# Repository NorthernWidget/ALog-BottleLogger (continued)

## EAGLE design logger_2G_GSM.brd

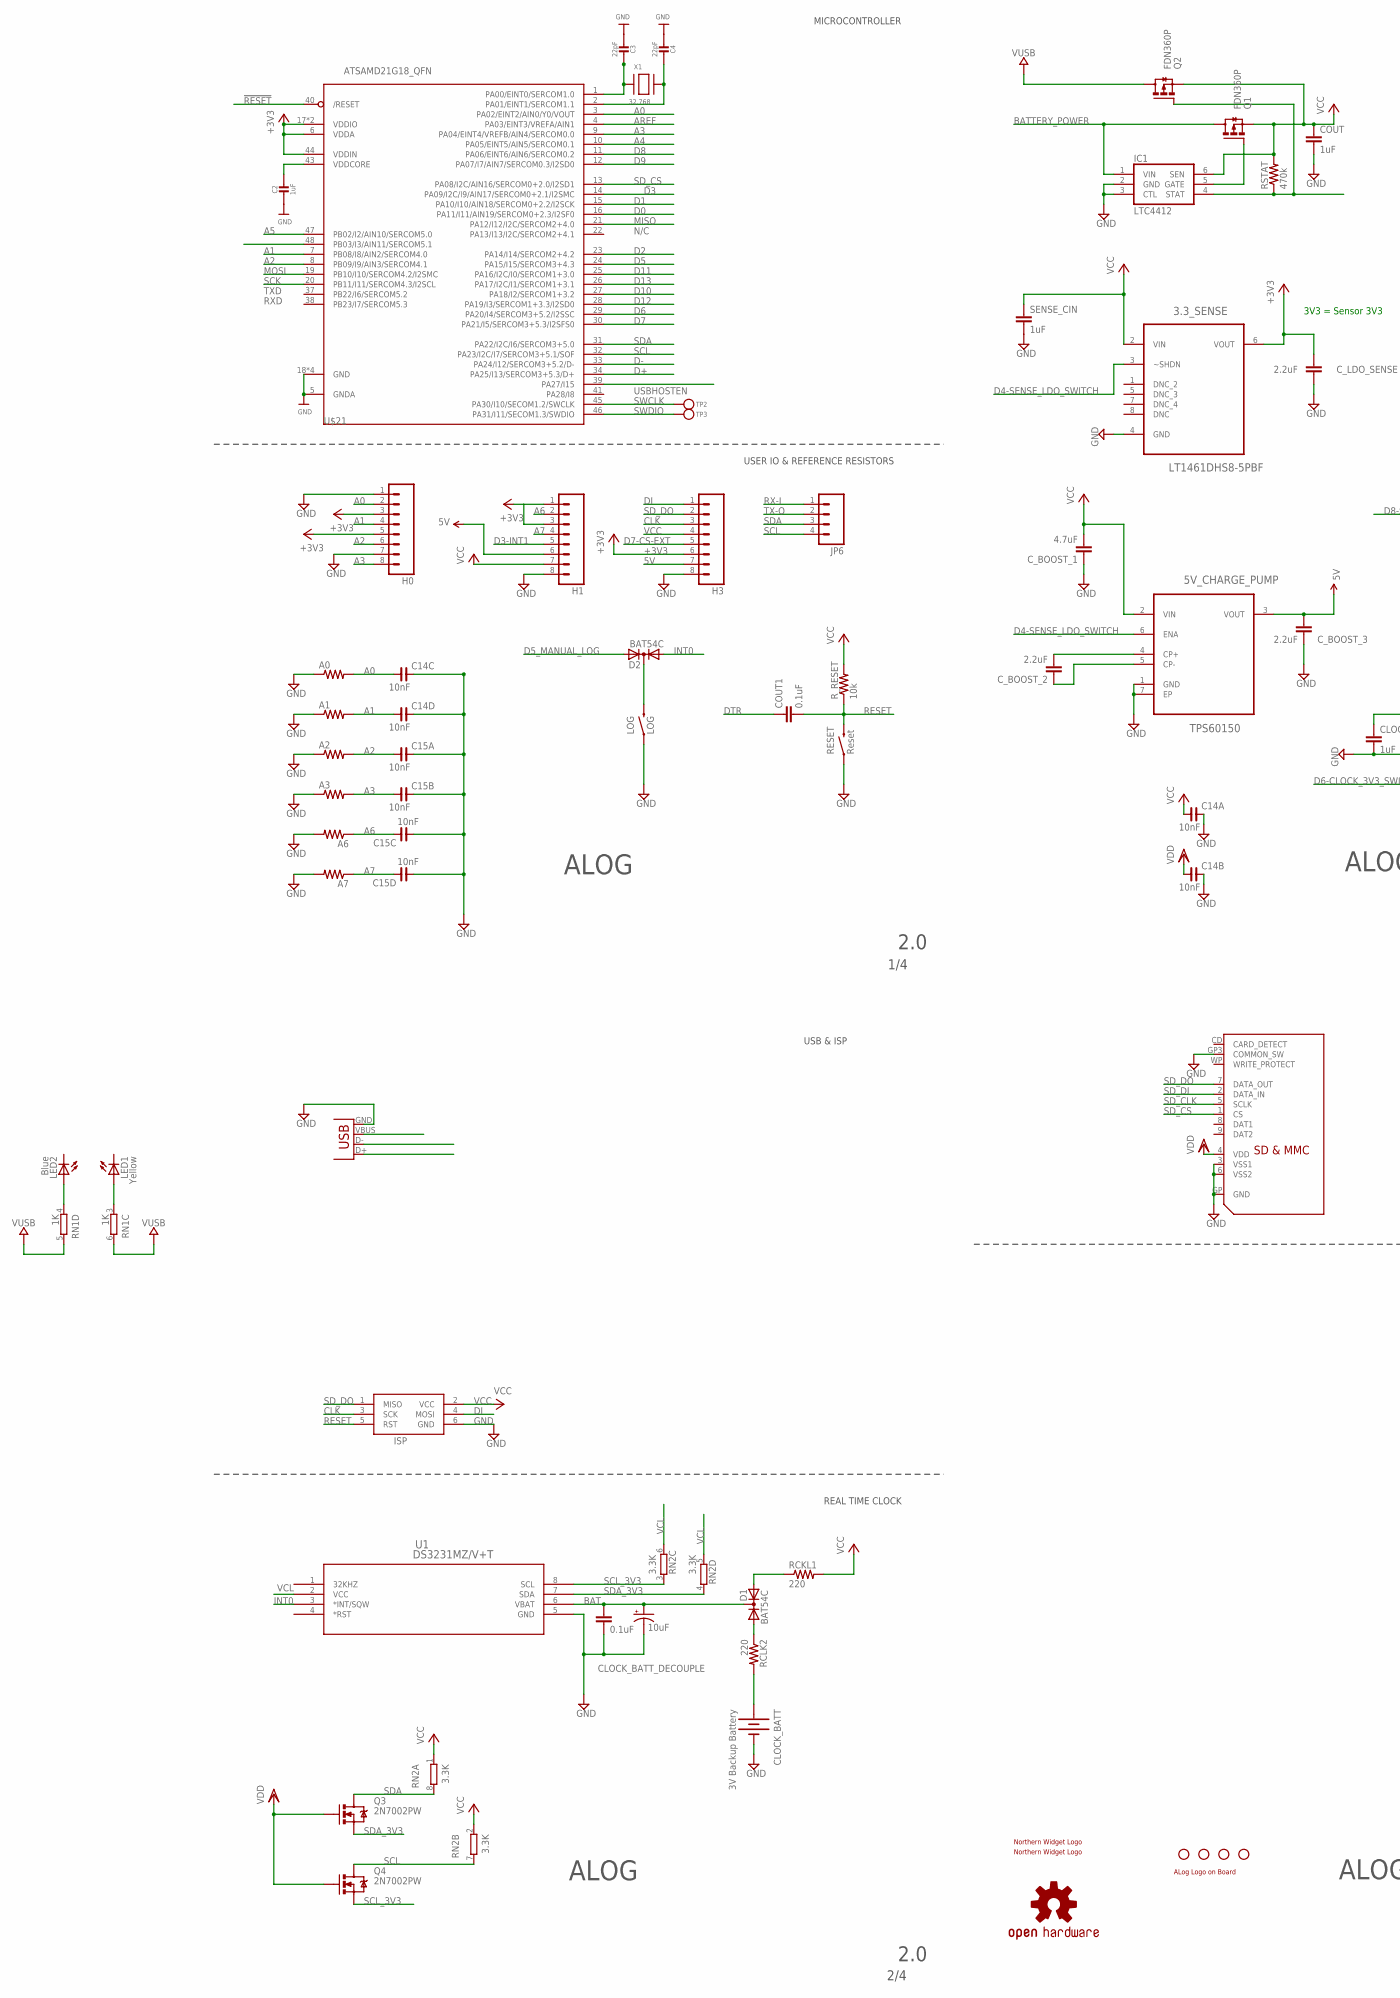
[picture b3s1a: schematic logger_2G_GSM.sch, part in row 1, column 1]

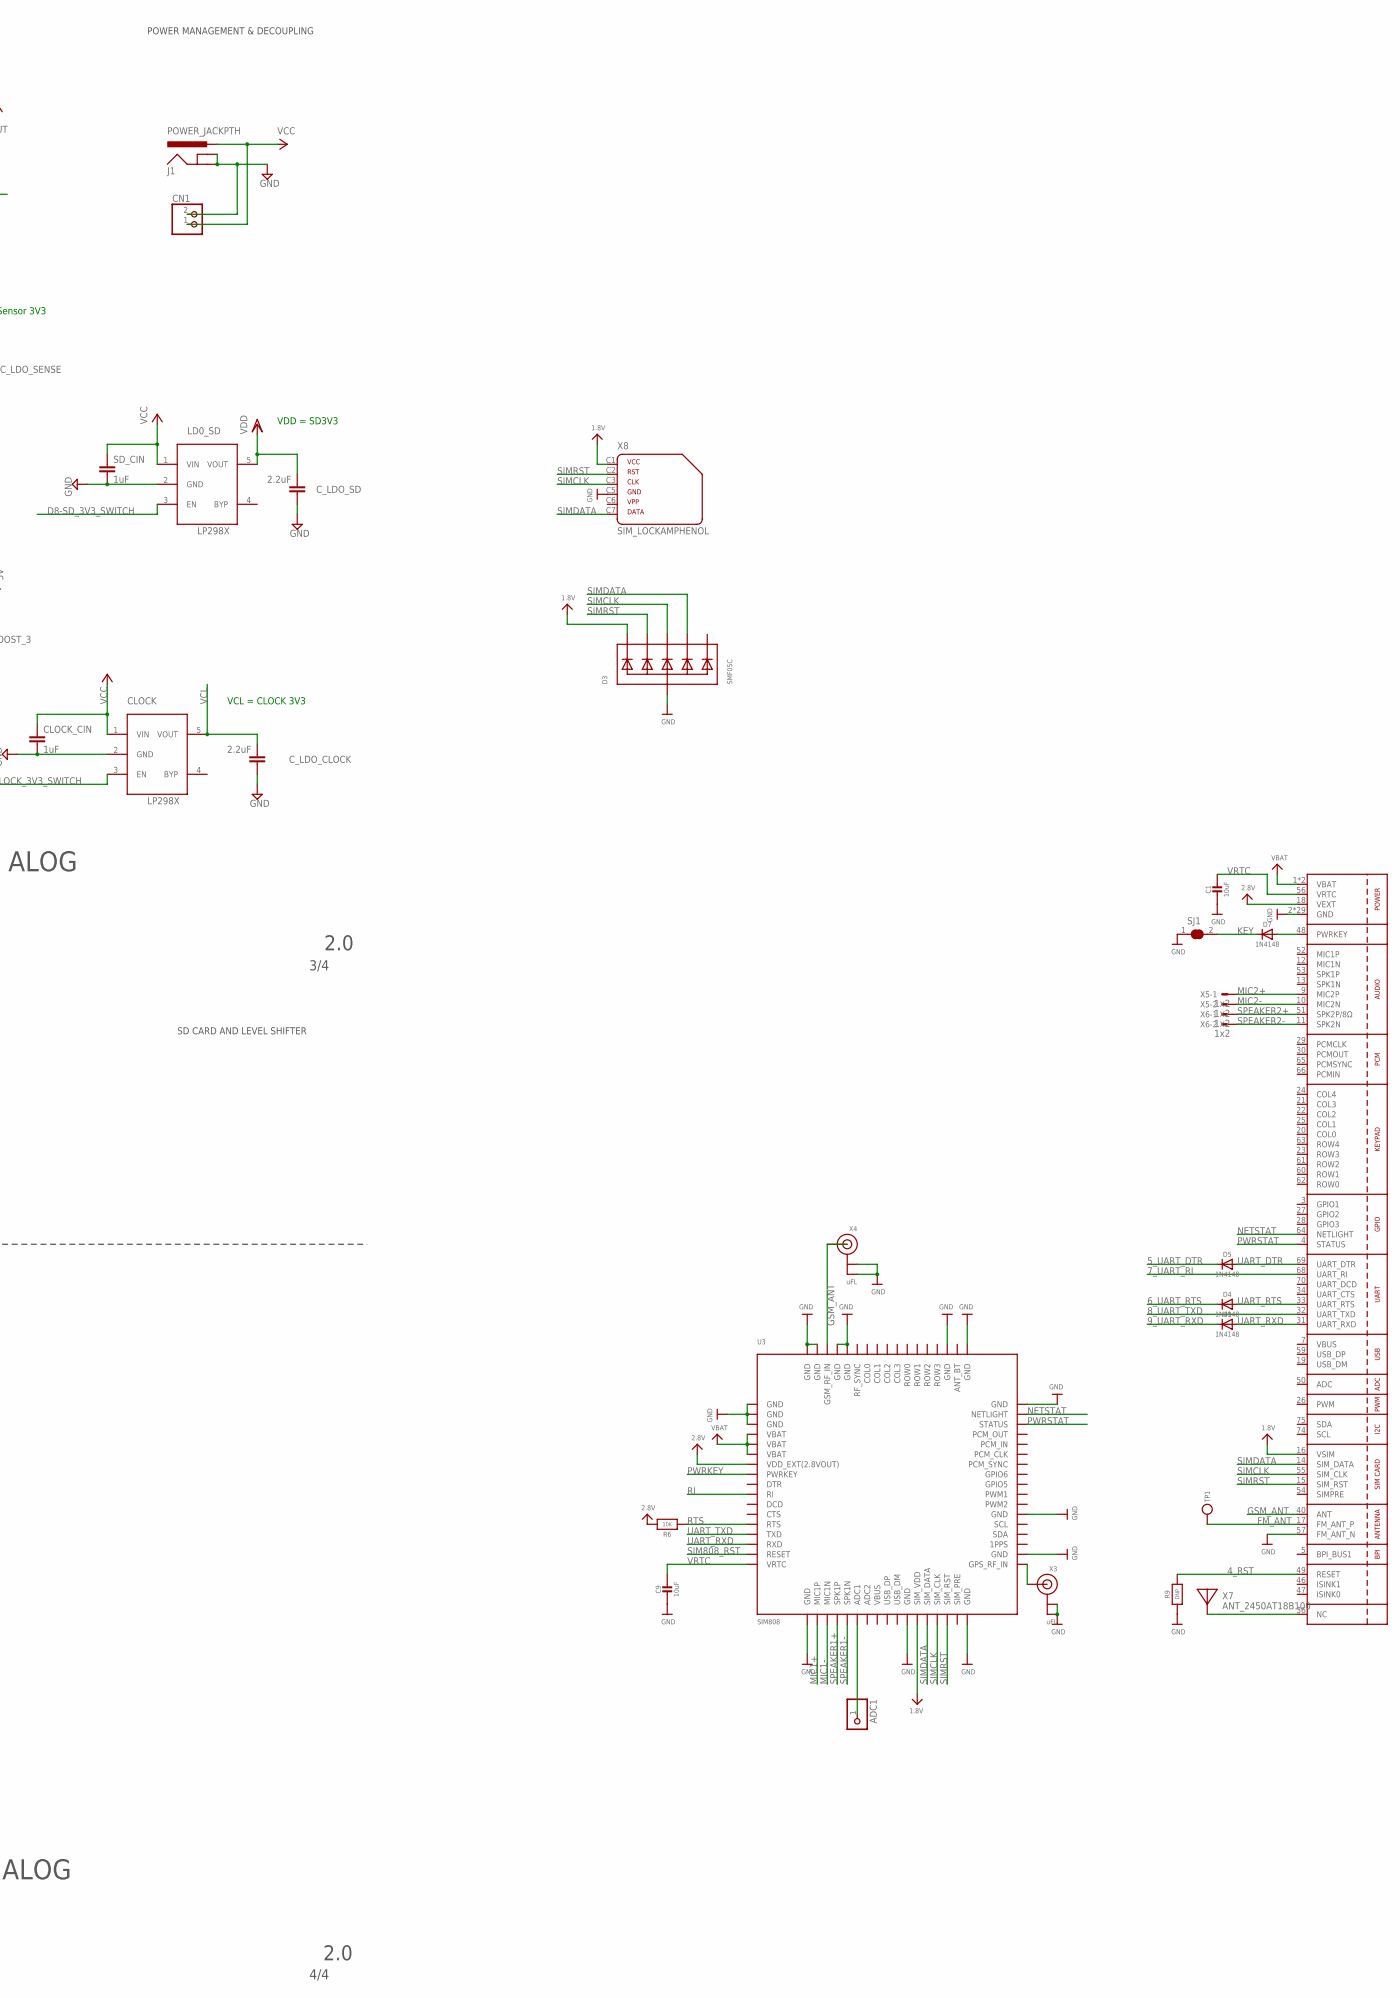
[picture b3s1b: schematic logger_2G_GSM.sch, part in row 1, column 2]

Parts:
3.3_SENSE: LT1461DHS8-5PBF; SOIC127P600X175-8N
5V_CHARGE_PUMP: TPS60150; SON65P200X200X80-7N
A0, A1, A2, A3, A6, A7: R-US_0207/10; 0207/10
ADC1: PINHD-1X1CB; 1X01-CLEANBIG
C1: 10uF; _0805MP
C2: 1uF; 0603-NO
C3, C4: 22pF; 0603-NO
C9: 10uF; 0805-NO
C14, C15: 10nF; CECJ-1206
CLOCK: LP2985; SOT23-5L
CLOCK_BATT: 3V Backup Battery; BATTCON_12MM_PTH
CLOCK_BATT_DECOUP: 0.1uF; C0603
CLOCK_BATT_DECOUPLE: 10uF; EIA3216
CLOCK_CIN: 1uF; C0603
CN1: JST_2PIN-THM; JST-PH-2-THM
COUT: 1uF; C0603
COUT1: 0.1uF; C0603
C_BOOST_1: 4.7uF; C0603
C_BOOST_2, C_BOOST_3: 2.2uF; C0603
C_LDO_CLOCK: 2.2uF; C0603
C_LDO_SD: 2.2uF; C0603
C_LDO_SENSE: 2.2uF; C0603
D1, D2: BAT54C; SOT23C
D3: SMF05C; SOT363
D4, D5, D7, D9: 1N4148; SOD-323
H0, H1, H3: M083.5MM-8; SCREWTERMINAL-3.5MM-8
IC1: LTC4412; TSOT23-6
ISP: AVRISP-6; AVRISP
J1: POWER_JACKPTH; POWER_JACK_PTH
JP1, JP2, JP3, JP4: STAND-OFF
JP5: USB-B; USB-B-PTH
JP6: M04SCREW; SCREWTERMINAL-3.5MM-4
LD0_SD: LP2985; SOT23-5L
LED1: Yellow; LED-0603
LED2: Blue; LED-0603
LOG: LOG; TACTILE-PTH
LOGO1: OSHW-LOGOM; OSHW-LOGO-M
Q1, Q2: FDN360P; SUPER-SOT3
Q3, Q4: 2N7002PW; SOT323
R6: 10K; 0805-NO
R9: DNP; 0603-NO
RCKL1: 220; R0603
RCLK2: 220; R0603
RESET: Reset; TACTILE-PTH
RN1: 1K; 0603-ARC
RN2: 3.3K; 0603-ARC
RSTAT: 470k; R0603
R_RESET: 10k; R0603
SD: SDMMC06132; 06132
SD_CIN: 1uF; C0603
SENSE_CIN: 1uF; C0603
SJ1: SOLDERJUMPER_CLOSED; SOLDERJUMPER_CLOSEDWIRE
TP1, TP2, TP3: TESTPOINTROUND1.5MM; TESTPOINT_ROUND_1.5MM
U1: DS3231MZ/V+T; 21-0041B_8
U2: SIM800H/L; SIM800L
U3: SIM808; SIM900_SMT
U$1: NWLOGO
U$2: ALOG_LOGO_V1_5.5MM; ALOG_LOGO_V1_SMALL
U$3: NWLOGO_MED
U$21: ATSAMD21G18_QFN; TQFN48_7MM
X1: 32.768; XTAL3215
X3, X4: uFL; U.FL
X5, X6: 1x2; 87758-0216
X7: ANT_2450AT18B100
X8: SIM_LOCKAMPHENOL; C707_10M006_512_2

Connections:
1.8V: D3.1 (C1), U2.16 (VSIM), U3.P$29 (SIM_VDD), X8.C1 (1)
2.8V: R6.2, U2.18 (VEXT), U3.P$7 (VDD_EXT(2.8VOUT))
4_RST: R9.2, U2.49 (RESET)
5V: 5V_CHARGE_PUMP.3 (VOUT), C_BOOST_3.2, H1.6, H3.7
5_UART_DTR: D5.C
6_UART_RTS: D4.C
7_UART_RI: U2.68 (UART_RI)
8_UART_TXD: U2.32 (UART_TXD)
9_UART_RXD: D9.C
!RESET: U$21.40 (/RESET)
+3V3: 3.3_SENSE.6 (VOUT), C_LDO_SENSE.2, H0.3, H0.5, H1.1, H1.3, H3.6, U$21.6 (VDDA), U$21.17 (VDDIO), U$21.36 (VDDIO), U$21.44 (VDDIN)
A0: A0.2, C14.C1 (1), H0.2, U$21.3 (PA02/EINT2/AIN0/Y0/VOUT)
A1: A1.2, C14.D1 (1), H0.4, U$21.7 (PB08/I8/AIN2/SERCOM4.0)
A2: A2.2, C15.A1 (1), H0.6, U$21.8 (PB09/I9/AIN3/SERCOM4.1)
A3: A3.2, C15.B1 (1), H0.8, U$21.9 (PA04/EINT4/VREFB/AIN4/SERCOM0.0)
A4: U$21.10 (PA05/EINT5/AIN5/SERCOM0.1)
A5: U$21.47 (PB02/I2/AIN10/SERCOM5.0)
A6: A6.1, C15.C2 (2), H1.2
A7: A7.1, C15.D2 (2), H1.4
AREF: U$21.4 (PA03/EINT3/VREFA/AIN1)
BAT: CLOCK_BATT_DECOUP.1, CLOCK_BATT_DECOUPLE.A (+), D1.3 (K), U1.6 (VBAT)
BATTERY_POWER: IC1.1 (VIN), Q1.3 (D)
CLK: H3.3, ISP.3 (SCK)
D0: U$21.16 (PA11/I11/AIN19/SERCOM0+2.3/I2SF0)
D1: U$21.15 (PA10/I10/AIN18/SERCOM0+2.2/I2SCK)
D2: U$21.23 (PA14/I14/SERCOM2+4.2)
D3: U$21.14 (PA09/I2C/I9/AIN17/SERCOM0+2.1/I2SMC)
D3-INT1: H1.5
D4-SENSE_LDO_SWITCH: 3.3_SENSE.3 (~SHDN), 5V_CHARGE_PUMP.6 (ENA)
D5: U$21.24 (PA15/I15/SERCOM3+4.3)
D5_MANUAL_LOG: D2.2 (A2)
D6: U$21.29 (PA20/I4/SERCOM3+5.2/I2SSC)
D6-CLOCK_3V3_SWITCH: CLOCK.3 (EN)
D7: U$21.30 (PA21/I5/SERCOM3+5.3/I2SFS0)
D7-CS-EXT: H3.5
D8: U$21.11 (PA06/EINT6/AIN6/SERCOM0.2)
D8-SD_3V3_SWITCH: LD0_SD.3 (EN)
D9: U$21.12 (PA07/I7/AIN7/SERCOM0.3/I2SD0)
D10: U$21.27 (PA18/I2/SERCOM1+3.2)
D11: U$21.25 (PA16/I2C/I0/SERCOM1+3.0)
D12: U$21.28 (PA19/I3/SERCOM1+3.3/I2SD0)
D13: U$21.26 (PA17/I2C/I1/SERCOM1+3.1)
D+: U$21.34 (PA25/I13/SERCOM3+5.3/D+)
D-: U$21.33 (PA24/I12/SERCOM3+5.2/D-)
DI: H3.1, ISP.4 (MOSI)
DTR: COUT1.1
FM_ANT: TP1.P$1, U2.17 (FM_ANT_P)
GND: 3.3_SENSE.4 (GND), 5V_CHARGE_PUMP.1 (GND), 5V_CHARGE_PUMP.7 (EP), A0.1, A1.1, A2.1, A3.1, A6.2, A7.2, C1.2, C2.2, C3.2, C4.2, C9.2, C14.A2 (2), C14.B2 (2), C14.C2 (2), C14.D2 (2), C15.A2 (2), C15.B2 (2), C15.C1 (1), C15.D1 (1), CLOCK.2 (GND), CLOCK_BATT.GND (-), CLOCK_BATT_DECOUP.2, CLOCK_BATT_DECOUPLE.C (-), CLOCK_CIN.2, CN1.2 (1), COUT.2, C_BOOST_1.1, C_BOOST_3.1, C_LDO_CLOCK.1, C_LDO_SD.1, C_LDO_SENSE.1, D3.2 (A), H0.1, H0.7, H1.8, H3.8, IC1.2 (GND), IC1.3 (CTL), ISP.6 (GND), J1.GND, J1.GNDBREAK, JP5.GND, LD0_SD.2 (GND), LOG.1, R9.1, RESET.1, SD.3 (VSS1), SD.6 (VSS2), SD.GP (GND), SD.GP3 (COMMON_SW), SD_CIN.2, SENSE_CIN.2, SJ1.1, U1.5 (GND), U2.2 (GND), U2.6 (GND), U2.8 (GND), U2.35 (GND), U2.37 (GND), U2.38 (GND), U2.39 (GND), U2.41 (GND), U2.43 (GND), U2.44 (GND), U2.45 (GND), U2.57 (FM_ANT_N), U2.58 (GND), U2.67 (GND), U2.71 (GND), U2.72 (GND), U2.73 (GND), U2.76 (GND), U2.77 (GND), U2.78 (GND), U2.79 (GND), U2.80 (GND), U2.81 (GND), U2.82 (GND), U2.83 (GND), U2.84 (GND), U2.85 (GND), U2.86 (GND), U2.87 (GND), U2.88 (GND), U3.P$1 (GND), U3.P$2 (GND), U3.P$3 (GND), U3.P$18 (GND), U3.P$28 (GND), U3.P$34 (GND), U3.P$36 (GND), U3.P$40 (GND), U3.P$51 (GND), U3.P$52 (GND), U3.P$54 (GND), U3.P$64 (GND), U3.P$65 (GND), U3.P$67 (GND), U3.P$68 (GND), U$21.5 (GNDA), U$21.18 (GND), U$21.35 (GND), U$21.42 (GND), U$21.THERMAL (GND), X3.1 (GND), X3.2 (GND), X4.1 (GND), X4.2 (GND), X8.C5 (4)
GSM_ANT: U2.40 (ANT), U3.P$66 (GSM_RF_IN), X4.3 (SIGNAL)
INT0: D2.1 (A1), U1.3 (*INT/SQW)
KEY: D7.C, SJ1.2
MIC1+: U3.P$19 (MIC1P)
MIC1-: U3.P$20 (MIC1N)
MIC2+: U2.9 (MIC2P), X5.1
MIC2-: U2.10 (MIC2N), X5.2
MISO: U$21.21 (PA12/I12/I2C/SERCOM2+4.0)
MOSI: U$21.19 (PB10/I10/SERCOM4.2/I2SMC)
unnamed: D1.1 (A1), RCLK2.1
unnamed: CLOCK_BATT.VCC@1 (+), RCLK2.2
unnamed: LED2.A, RN1.4 (1)
unnamed: U3.P$35 (GPS_RF_IN), X3.3 (SIGNAL)
unnamed: IC1.4 (STAT), Q2.1 (G), RSTAT.1
unnamed: IC1.5 (GATE), Q1.1 (G)
unnamed: LED1.A, RN1.3 (1)
unnamed: ADC1.1, U3.P$23 (ADC1)
unnamed: D2.3 (K), LOG.3 (2)
unnamed: U2.36 (NC), X7.FP
unnamed: 5V_CHARGE_PUMP.4 (CP+), C_BOOST_2.2
unnamed: 5V_CHARGE_PUMP.5 (CP-), C_BOOST_2.1
unnamed: D7.A, U2.48 (PWRKEY)
unnamed: C3.1, U$21.1 (PA00/EINT0/SERCOM1.0), X1.P$1
unnamed: C4.1, U$21.2 (PA01/EINT1/SERCOM1.1), X1.P$2
unnamed: D1.2 (A2), RCKL1.1
NETSTAT: U2.64 (NETLIGHT), U3.P$50 (NETLIGHT)
PWRKEY: U3.P$8 (PWRKEY)
PWRSTAT: U2.4 (STATUS), U3.P$49 (STATUS)
RESET: COUT1.2, ISP.5 (RST), RESET.3 (2), R_RESET.1
RI: U3.P$10 (RI)
RTS: R6.1, U3.P$13 (RTS)
RX-I: JP6.1
SCK: U$21.20 (PB11/I11/SERCOM4.3/I2SCL)
SCL: JP6.4, Q4.3 (D), RN2.7 (2), U$21.32 (PA23/I2C/I7/SERCOM3+5.1/SOF)
SCL_3V3: Q4.2 (S), RN2.3 (1), U1.8 (SCL)
SDA: JP6.3, Q3.3 (D), RN2.8 (2), U$21.31 (PA22/I2C/I6/SERCOM3+5.0)
SDA_3V3: Q3.2 (S), RN2.4 (1), U1.7 (SDA)
SD_CLK: SD.5 (SCLK)
SD_CS: SD.1 (CS), U$21.13 (PA08/I2C/AIN16/SERCOM0+2.0/I2SD1)
SD_DI: SD.2 (DATA_IN)
SD_DO: H3.2, ISP.1 (MISO), SD.7 (DATA_OUT)
SIM808_RST: U3.P$16 (RESET)
SIMCLK: D3.4 (C3), U2.55 (SIM_CLK), U3.P$31 (SIM_CLK), X8.C3 (3)
SIMDATA: D3.5 (C4), U2.14 (SIM_DATA), U3.P$30 (SIM_DATA), X8.C7 (6)
SIMRST: D3.3 (C2), U2.15 (SIM_RST), U3.P$32 (SIM_RST), X8.C2 (2)
SPEAKER1+: U3.P$21 (SPK1P)
SPEAKER1-: U3.P$22 (SPK1N)
SPEAKER2+: U2.51 (SPK2P/8Ω), X6.1
SPEAKER2-: U2.11 (SPK2N), X6.2
SWCLK: TP2.P$1, U$21.45 (PA30/I10/SECOM1.2/SWCLK)
SWDIO: TP3.P$1, U$21.46 (PA31/I11/SECOM1.3/SWDIO)
TX-O: JP6.2
UART_DTR: D5.A, U2.69 (UART_DTR)
UART_RTS: D4.A, U2.33 (UART_RTS)
UART_RXD: D9.A, U2.31 (UART_RXD), U3.P$15 (RXD)
UART_TXD: U3.P$14 (TXD)
VBAT: U2.1 (VBAT), U2.42 (VBAT), U3.P$4 (VBAT), U3.P$5 (VBAT), U3.P$6 (VBAT)
VBUS: U2.7 (VBUS), U3.P$25 (VBUS)
VCC: 3.3_SENSE.2 (VIN), 5V_CHARGE_PUMP.2 (VIN), C14.A1 (1), CLOCK.1 (VIN), CLOCK_CIN.1, CN1.1 (2), COUT.1, C_BOOST_1.2, H1.7, H3.4, IC1.6 (SEN), ISP.2 (VCC), J1.PWR, LD0_SD.1 (VIN), Q1.2 (S), Q2.2 (S), RCKL1.2, RN2.1, RN2.2 (1), RSTAT.2, R_RESET.2, SD_CIN.1, SENSE_CIN.1
VCL: CLOCK.5 (VOUT), C_LDO_CLOCK.2, RN2.5 (2), RN2.6 (2), U1.2 (VCC)
VDD: C14.B1 (1), C_LDO_SD.2, LD0_SD.5 (VOUT), Q3.1 (G), Q4.1 (G), SD.4 (VDD)
VDDCORE: C2.1, U$21.43 (VDDCORE)
VRTC: C1.1, C9.1, U2.56 (VRTC), U3.P$17 (VRTC)
VUSB: Q2.3 (D), RN1.5 (2), RN1.6 (2)

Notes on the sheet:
VDD = SD3V3
3V3 = Sensor 3V3
VCL = CLOCK 3V3
MICROCONTROLLER
USER IO & REFERENCE RESISTORS
ALOG
USB & ISP
REAL TIME CLOCK
SD CARD AND LEVEL SHIFTER
POWER MANAGEMENT & DECOUPLING
2.0
1/4
2/4
3/4
4/4
N/C
USBHOSTEN
TXD
RXD

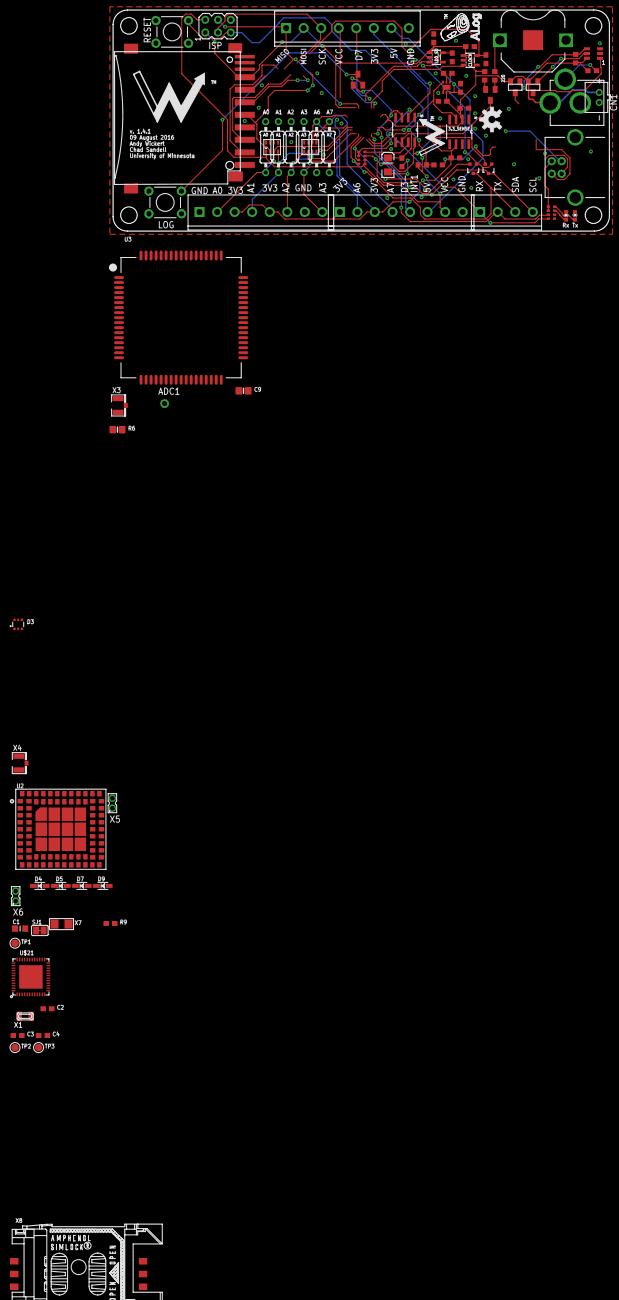
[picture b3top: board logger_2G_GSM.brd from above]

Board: 2 copper layers, 99.0 x 44.1 mm, 88 parts (0 on the bottom side), 67 nets.

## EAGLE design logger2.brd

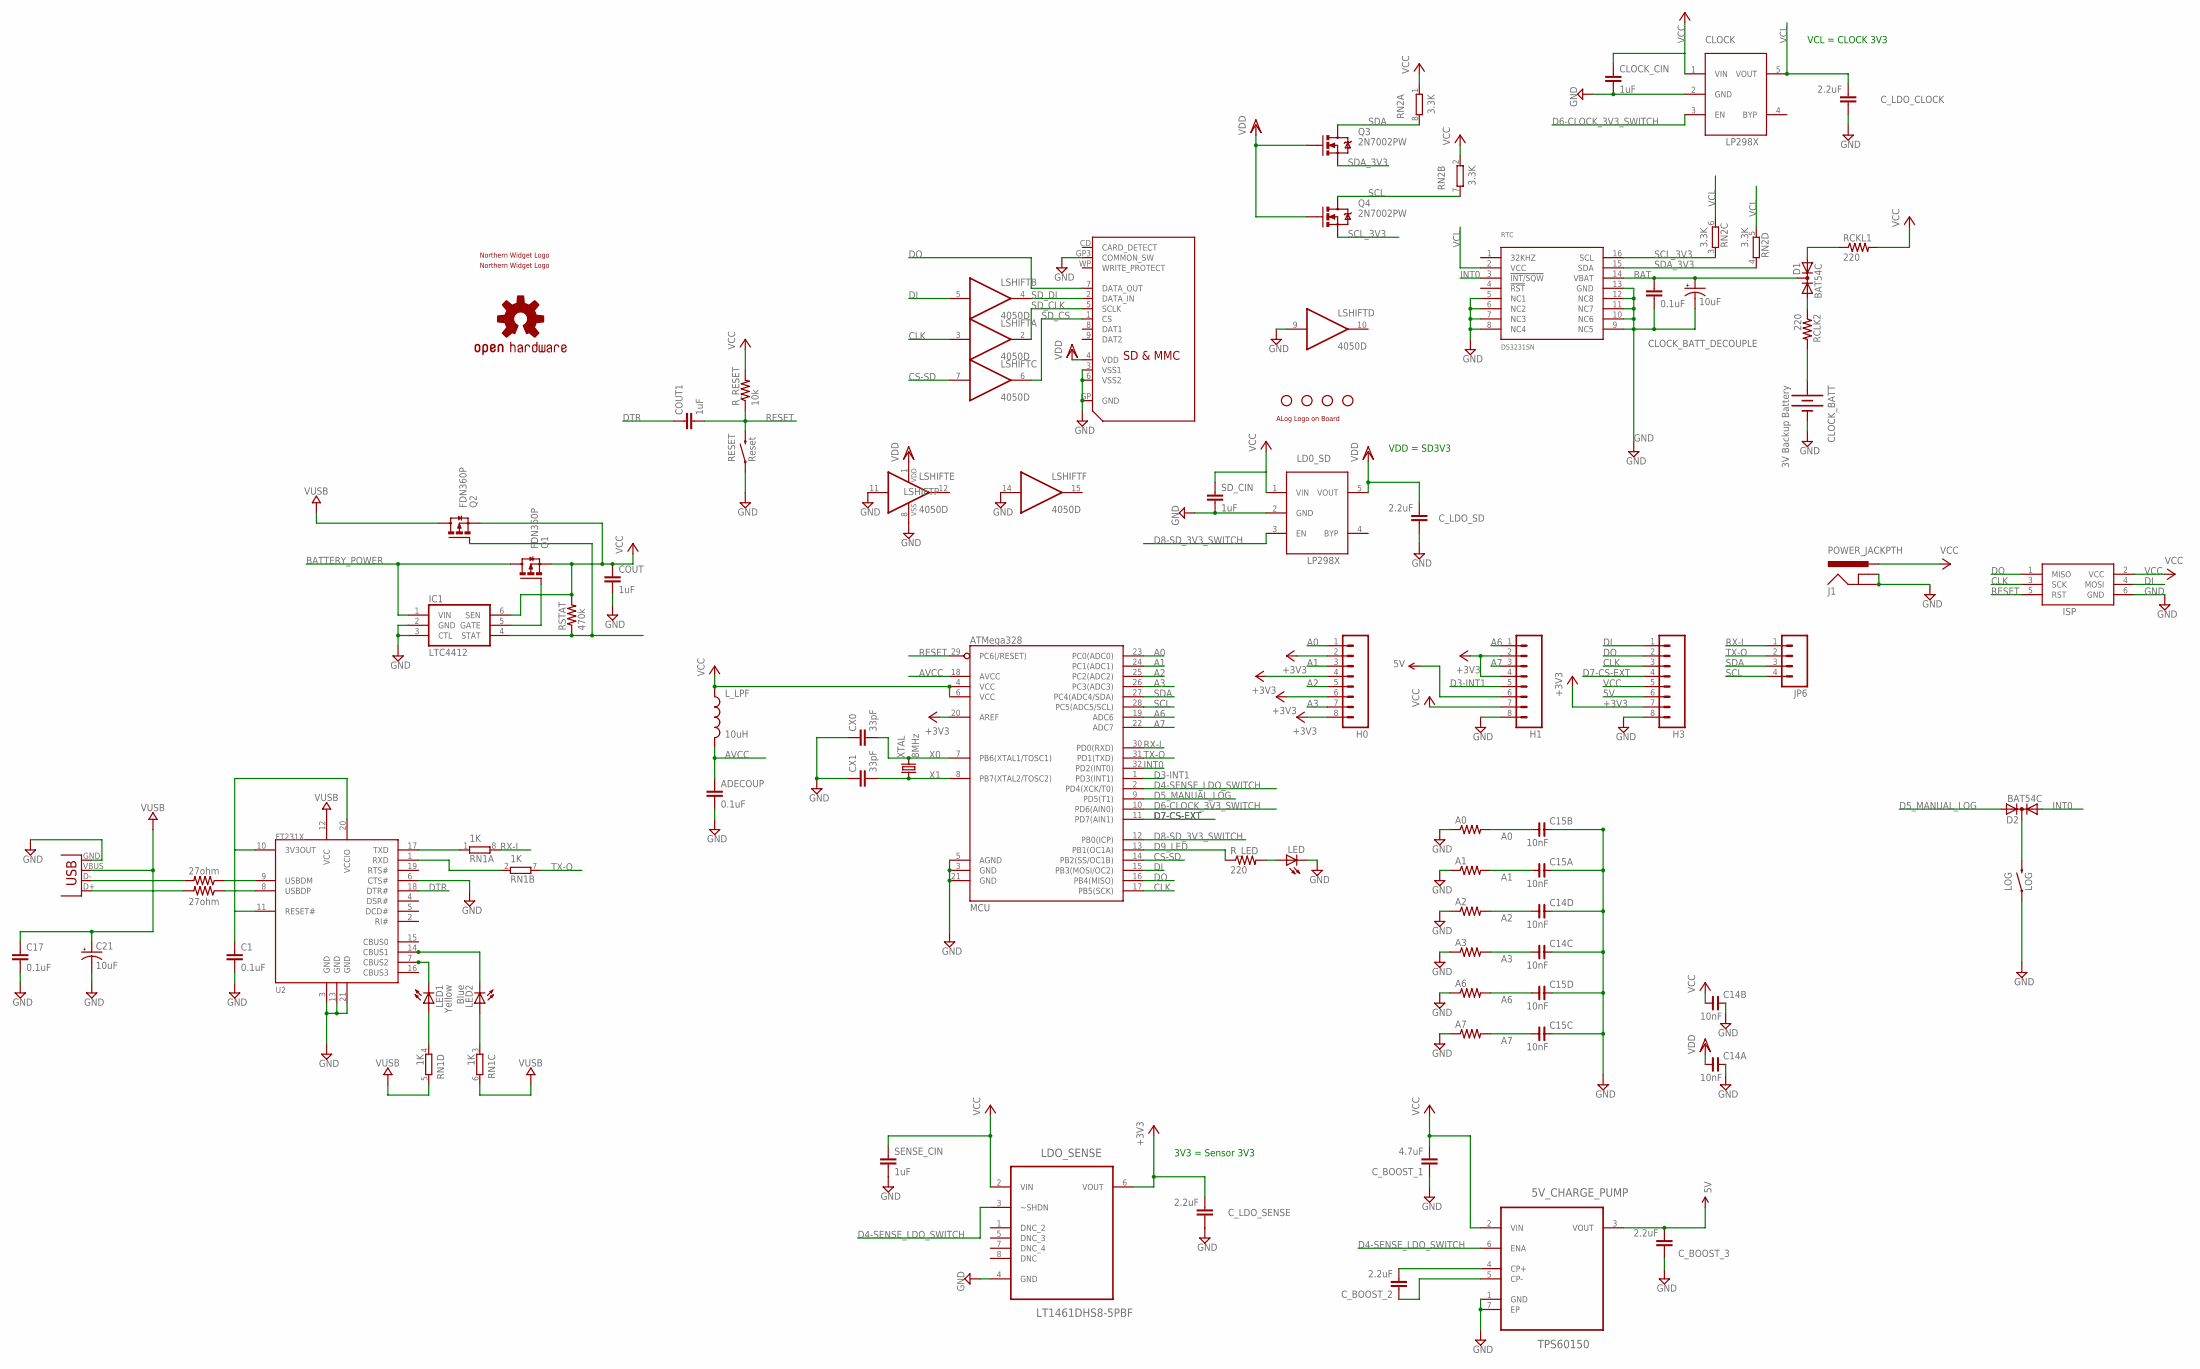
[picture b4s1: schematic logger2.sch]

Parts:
5V_CHARGE_PUMP: TPS60150; SON65P200X200X80-7N
A0, A1, A2, A3, A6, A7: R-US_0207/10; 0207/10
ADECOUP: 0.1uF; C0603
C1, C17: 0.1uF; C0603
C14, C15: 10nF; CECJ-1206
C21: 10uF; EIA3216
CLOCK: LP2985; SOT23-5L
CLOCK_BATT: 3V Backup Battery; BATTCON_12MM_PTH
CLOCK_BATT_DECOUP: 0.1uF; C0603
CLOCK_BATT_DECOUPLE: 10uF; EIA3216
CLOCK_CIN: 1uF; C0603
COUT, COUT1: 1uF; C0603
CX0, CX1: 33pF; C0603
C_BOOST_1: 4.7uF; C0603
C_BOOST_2, C_BOOST_3: 2.2uF; C0603
C_LDO_CLOCK: 2.2uF; C0603
C_LDO_SD: 2.2uF; C0603
C_LDO_SENSE: 2.2uF; C0603
D1, D2: BAT54C; SOT23C
D+: 27ohm; R0603
D-: 27ohm; R0603
H0, H1, H3: M083.5MM-8; SCREWTERMINAL-3.5MM-8
IC1: LTC4412; TSOT23-6
ISP: AVRISP-6; AVRISP
J1: POWER_JACKPTH; POWER_JACK_PTH
JP1, JP2, JP3, JP4: STAND-OFF
JP5: USB-B; USB-B-PTH
JP6: M04SCREW; SCREWTERMINAL-3.5MM-4
LD0_SD: LP2985; SOT23-5L
LDO_SENSE: LT1461DHS8-5PBF; SOIC127P600X175-8N
LED: LED3MM
LED1: Yellow; LED-0603
LED2: Blue; LED-0603
LOG: LOG; TACTILE-PTH
LOGO1: OSHW-LOGOM; OSHW-LOGO-M
LSHIFT: 4050D; SO16
L_LPF: 10uH; 0805
MCU: ATMega328; TQFP32-08
Q1, Q2: FDN360P; SUPER-SOT3
Q3, Q4: 2N7002PW; SOT323
RCKL1: 220; R0603
RCLK2: 220; R0603
RESET: Reset; TACTILE-PTH
RN1: 1K; 0603-ARC
RN2: 3.3K; 0603-ARC
RSTAT: 470k; R0603
RTC: DS3231SN; SO16W
R_LED: 220; R0603
R_RESET: 10k; R0603
SD: SDMMC06132; 06132
SD_CIN: 1uF; C0603
SENSE_CIN: 1uF; C0603
U2: FT231X-Q; QFN20
U$1: NWLOGO
U$2: ALOG_LOGO_V1_5.5MM; ALOG_LOGO_V1_SMALL
U$3: NWLOGO_MED
XTAL: 8MHz; HC49U-V

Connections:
5V: 5V_CHARGE_PUMP.3 (VOUT), C_BOOST_3.2, H1.6, H3.6
+3V3: C_LDO_SENSE.2, H0.2, H0.4, H0.6, H0.8, H1.2, H1.4, H3.7, LDO_SENSE.6 (VOUT), MCU.20 (AREF)
A0: A0.2, C15.B1 (1), H0.1, MCU.23 (PC0(ADC0))
A1: A1.2, C15.A1 (1), H0.3, MCU.24 (PC1(ADC1))
A2: A2.2, C14.D1 (1), H0.5, MCU.25 (PC2(ADC2))
A3: A3.2, C14.C1 (1), H0.7, MCU.26 (PC3(ADC3))
A6: A6.2, C15.D1 (1), H1.1, MCU.19 (ADC6)
A7: A7.2, C15.C1 (1), H1.3, MCU.22 (ADC7)
AVCC: ADECOUP.1, L_LPF.2, MCU.18 (AVCC)
BAT: CLOCK_BATT_DECOUP.1, CLOCK_BATT_DECOUPLE.A (+), D1.3 (K), RTC.14 (VBAT)
BATTERY_POWER: IC1.1 (VIN), Q1.3 (D)
CLK: H3.3, ISP.3 (SCK), LSHIFT.3 (I), MCU.17 (PB5(SCK))
CS-SD: LSHIFT.7 (I), MCU.14 (PB2(SS/OC1B))
D3-INT1: H1.5, MCU.1 (PD3(INT1))
D4-SENSE_LDO_SWITCH: 5V_CHARGE_PUMP.6 (ENA), LDO_SENSE.3 (~SHDN), MCU.2 (PD4(XCK/T0))
D5_MANUAL_LOG: D2.2 (A2), MCU.9 (PD5(T1))
D6-CLOCK_3V3_SWITCH: CLOCK.3 (EN), MCU.10 (PD6(AIN0))
D7-CS-EXT: H3.4, MCU.11 (PD7(AIN1))
D8-SD_3V3_SWITCH: LD0_SD.3 (EN), MCU.12 (PB0(ICP))
D9_LED: MCU.13 (PB1(OC1A)), R_LED.1
DI: H3.1, ISP.4 (MOSI), LSHIFT.5 (I), MCU.15 (PB3(MOSI/OC2))
DO: H3.2, ISP.1 (MISO), MCU.16 (PB4(MISO)), SD.7 (DATA_OUT)
DTR: COUT1.1, U2.18 (DTR#)
GND: 5V_CHARGE_PUMP.1 (GND), 5V_CHARGE_PUMP.7 (EP), A0.1, A1.1, A2.1, A3.1, A6.1, A7.1, ADECOUP.2, C1.2, C14.A2 (2), C14.B2 (2), C14.C2 (2), C14.D2 (2), C15.A2 (2), C15.B2 (2), C15.C2 (2), C15.D2 (2), C17.2, C21.C (-), CLOCK.2 (GND), CLOCK_BATT.GND (-), CLOCK_BATT_DECOUP.2, CLOCK_BATT_DECOUPLE.C (-), CLOCK_CIN.2, COUT.2, CX0.1, CX1.1, C_BOOST_1.1, C_BOOST_3.1, C_LDO_CLOCK.1, C_LDO_SD.1, C_LDO_SENSE.1, H1.8, H3.8, IC1.2 (GND), IC1.3 (CTL), ISP.6 (GND), J1.GND, J1.GNDBREAK, JP5.GND, LD0_SD.2 (GND), LDO_SENSE.4 (GND), LED.K (C), LOG.1, LSHIFT.8 (VSS), LSHIFT.9 (I), LSHIFT.11 (I), LSHIFT.14 (I), MCU.3 (GND), MCU.5 (AGND), MCU.21 (GND), RESET.1, RTC.5 (NC1), RTC.6 (NC2), RTC.7 (NC3), RTC.8 (NC4), RTC.9 (NC5), RTC.10 (NC6), RTC.11 (NC7), RTC.12 (NC8), RTC.13 (GND), SD.3 (VSS1), SD.6 (VSS2), SD.GP (GND), SD.GP3 (COMMON_SW), SD_CIN.2, SENSE_CIN.2, U2.3 (GND), U2.6 (CTS#), U2.13 (GND), U2.21 (GND)
INT0: D2.1 (A1), MCU.32 (PD2(INT0)), RTC.3 (!INT/SQW)
LED+: LED.A, R_LED.2
unnamed: D1.1 (A1), RCLK2.1
unnamed: CLOCK_BATT.VCC@1 (+), RCLK2.2
unnamed: D+.2, JP5.D+
unnamed: D-.2, JP5.D-
unnamed: LED1.C, U2.7 (CBUS2)
unnamed: LED2.C, U2.14 (CBUS1)
unnamed: IC1.4 (STAT), Q2.1 (G), RSTAT.1
unnamed: IC1.5 (GATE), Q1.1 (G)
unnamed: LED1.A, RN1.4 (1)
unnamed: LED2.A, RN1.3 (1)
unnamed: D2.3 (K), LOG.3 (2)
unnamed: D-.1, U2.9 (USBDM)
unnamed: 5V_CHARGE_PUMP.4 (CP+), C_BOOST_2.2
unnamed: 5V_CHARGE_PUMP.5 (CP-), C_BOOST_2.1
unnamed: D+.1, U2.8 (USBDP)
unnamed: C1.1, U2.10 (3V3OUT), U2.11 (RESET#), U2.20 (VCCIO)
unnamed: RN1.1, U2.17 (TXD)
unnamed: RN1.2 (1), U2.1 (RXD)
unnamed: D1.2 (A2), RCKL1.1
RESET: COUT1.2, ISP.5 (RST), MCU.29 (PC6(/RESET)), RESET.3 (2), R_RESET.1
RX-I: JP6.1, MCU.30 (PD0(RXD)), RN1.8 (2)
SCL: JP6.4, MCU.28 (PC5(ADC5/SCL)), Q4.3 (D), RN2.7 (2)
SCL_3V3: Q4.2 (S), RN2.3 (1), RTC.16 (SCL)
SDA: JP6.3, MCU.27 (PC4(ADC4/SDA)), Q3.3 (D), RN2.8 (2)
SDA_3V3: Q3.2 (S), RN2.4 (1), RTC.15 (SDA)
SD_CLK: LSHIFT.2 (O), SD.5 (SCLK)
SD_CS: LSHIFT.6 (O), SD.1 (CS)
SD_DI: LSHIFT.4 (O), SD.2 (DATA_IN)
TX-O: JP6.2, MCU.31 (PD1(TXD)), RN1.7 (2)
VCC: 5V_CHARGE_PUMP.2 (VIN), C14.B1 (1), CLOCK.1 (VIN), CLOCK_CIN.1, COUT.1, C_BOOST_1.2, H1.7, H3.5, IC1.6 (SEN), ISP.2 (VCC), J1.PWR, LD0_SD.1 (VIN), LDO_SENSE.2 (VIN), L_LPF.1, MCU.4 (VCC), MCU.6 (VCC), Q1.2 (S), Q2.2 (S), RCKL1.2, RN2.1, RN2.2 (1), RSTAT.2, R_RESET.2, SD_CIN.1, SENSE_CIN.1
VCL: CLOCK.5 (VOUT), C_LDO_CLOCK.2, RN2.5 (2), RN2.6 (2), RTC.2 (VCC)
VDD: C14.A1 (1), C_LDO_SD.2, LD0_SD.5 (VOUT), LSHIFT.1 (VDD), Q3.1 (G), Q4.1 (G), SD.4 (VDD)
VUSB: C17.1, C21.A (+), JP5.VBUS, Q2.3 (D), RN1.5 (2), RN1.6 (2), U2.12 (VCC)
X0: CX0.2, MCU.7 (PB6(XTAL1/TOSC1)), XTAL.2
X1: CX1.2, MCU.8 (PB7(XTAL2/TOSC2)), XTAL.1

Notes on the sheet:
VDD = SD3V3
3V3 = Sensor 3V3
VCL = CLOCK 3V3

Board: 2 copper layers, 75 parts (0 on the bottom side), 61 nets, no tracks yet.

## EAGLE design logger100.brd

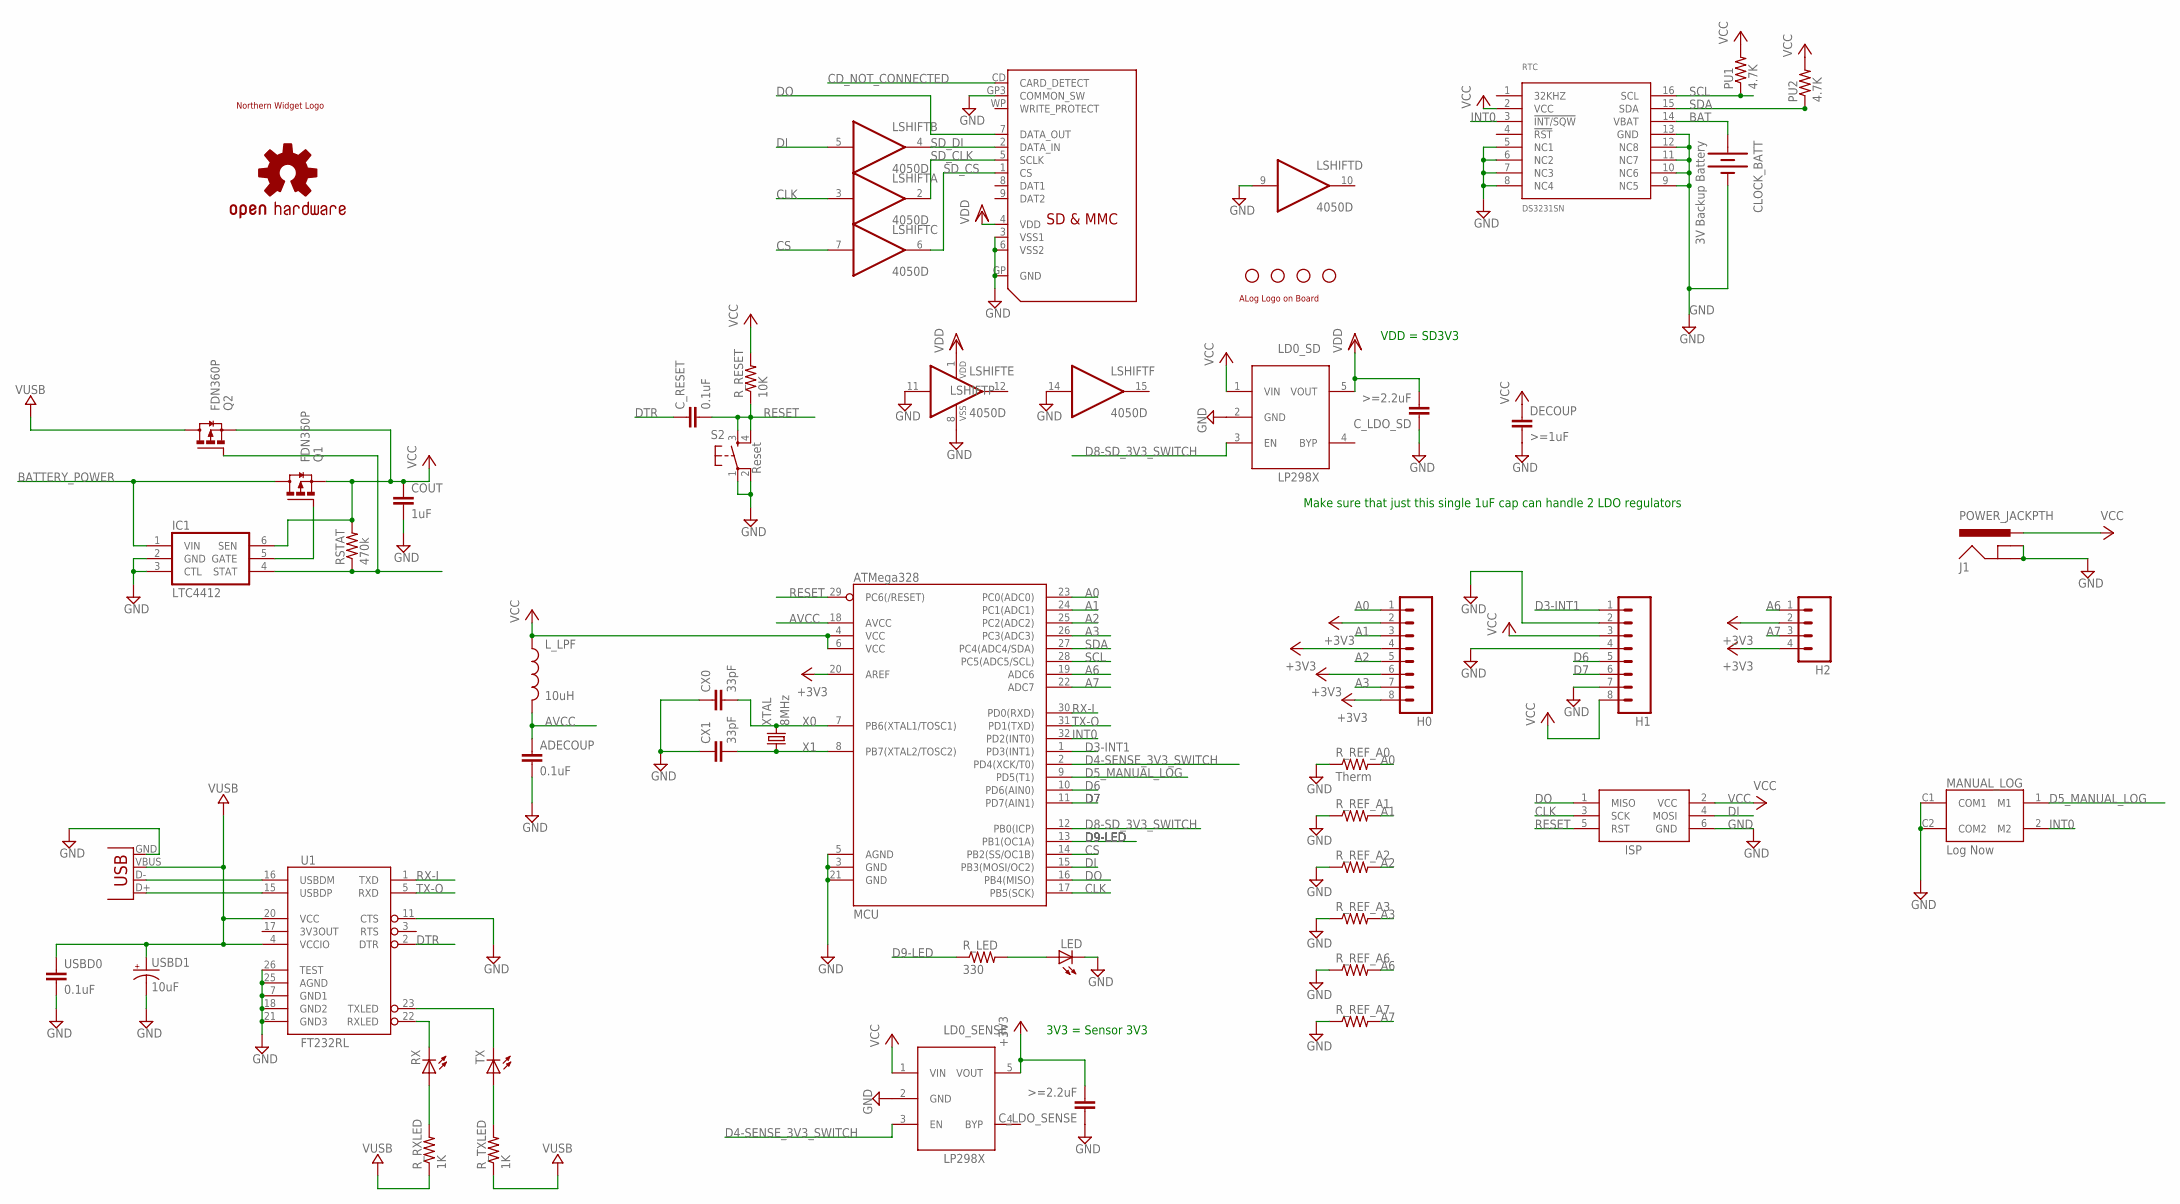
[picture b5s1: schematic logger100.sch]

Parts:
ADECOUP: 0.1uF; C0603
CLOCK_BATT: 3V Backup Battery; BATTCON_12MM_PTH
COUT: 1uF; C0603-ROUND
CX0, CX1: 33pF; C0603
C_LDO_SD: >=2.2uF; C0603
C_LDO_SENSE: >=2.2uF; C0603
C_RESET: 0.1uF; C0603
DECOUP: >=1uF; C0603
H0, H1: M083.5MM-8; SCREWTERMINAL-3.5MM-8
H2: M04SCREW; SCREWTERMINAL-3.5MM-4
IC1: LTC4412; TSOT23-6
ISP: AVRISP-6; AVRISP
J1: POWER_JACKPTH; POWER_JACK_PTH
JP1, JP2, JP3, JP4: STAND-OFF
JP5: USB-B; USB-B-PTH
LD0_SD, LD0_SENSE: LP2985; SOT23-5L
LED: LED3MM
LOGO1: OSHW-LOGOM; OSHW-LOGO-M
LSHIFT: 4050D; SO16
L_LPF: 10uH; 0805
MANUAL_LOG: Log Now; TL_BUTTON
MCU: ATMega328; TQFP32-08
PU1, PU2: 4.7K; R0603
Q1, Q2: FDN360P; SUPER-SOT3
RSTAT: 470k; R0603
RTC: DS3231SN; SO16W
RX: LED0603; LED-0603
R_LED: 330; R0603
R_REF_A0: Therm; 0207/10
R_REF_A1, R_REF_A2, R_REF_A3, R_REF_A6, R_REF_A7: R-US_0207/10; 0207/10
R_RESET: 10K; R0603
R_RXLED: 1K; R0603
R_TXLED: 1K; R0603
S2: Reset; TACTILE_SWITCH_SMD
SD: SDMMC06132; 06132
TX: LED0603; LED-0603
U1: FT232RL; SSOP28DB
U$1: NWLOGO
U$2: ALOG_LOGO_V1_5.5MM; ALOG_LOGO_V1_SMALL
USBD0: 0.1uF; C0603
USBD1: 10uF; EIA3216
XTAL: 8MHz; HC49U-V

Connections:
+3V3: C_LDO_SENSE.2, H0.2, H0.4, H0.6, H0.8, H2.2, H2.4, LD0_SENSE.5 (VOUT), MCU.20 (AREF)
A0: H0.1, MCU.23 (PC0(ADC0)), R_REF_A0.2
A1: H0.3, MCU.24 (PC1(ADC1)), R_REF_A1.2
A2: H0.5, MCU.25 (PC2(ADC2)), R_REF_A2.2
A3: H0.7, MCU.26 (PC3(ADC3)), R_REF_A3.2
A6: H2.1, MCU.19 (ADC6), R_REF_A6.2
A7: H2.3, MCU.22 (ADC7), R_REF_A7.2
AVCC: ADECOUP.1, L_LPF.2, MCU.18 (AVCC)
BAT: CLOCK_BATT.VCC@1 (+), RTC.14 (VBAT)
BATTERY_POWER: IC1.1 (VIN), Q1.3 (D)
CD_NOT_CONNECTED: SD.CD (CARD_DETECT)
CLK: ISP.3 (SCK), LSHIFT.3 (I), MCU.17 (PB5(SCK))
CS: LSHIFT.7 (I), MCU.14 (PB2(SS/OC1B))
D3-INT1: H1.1, MCU.1 (PD3(INT1))
D4-SENSE_3V3_SWITCH: LD0_SENSE.3 (EN), MCU.2 (PD4(XCK/T0))
D5_MANUAL_LOG: MANUAL_LOG.1 (M1), MCU.9 (PD5(T1))
D6: H1.5, MCU.10 (PD6(AIN0))
D7: H1.6, MCU.11 (PD7(AIN1))
D8-SD_3V3_SWITCH: LD0_SD.3 (EN), MCU.12 (PB0(ICP))
D9-LED: MCU.13 (PB1(OC1A)), R_LED.1
DI: ISP.4 (MOSI), LSHIFT.5 (I), MCU.15 (PB3(MOSI/OC2))
DO: ISP.1 (MISO), MCU.16 (PB4(MISO)), SD.7 (DATA_OUT)
DTR: C_RESET.1, U1.2 (DTR)
GND: ADECOUP.2, CLOCK_BATT.GND (-), COUT.2, CX0.1, CX1.1, C_LDO_SD.1, C_LDO_SENSE.1, DECOUP.2, H1.2, H1.4, H1.7, IC1.2 (GND), IC1.3 (CTL), ISP.6 (GND), J1.GND, J1.GNDBREAK, JP5.GND, LD0_SD.2 (GND), LD0_SENSE.2 (GND), LED.K (C), LSHIFT.8 (VSS), LSHIFT.9 (I), LSHIFT.11 (I), LSHIFT.14 (I), MANUAL_LOG.C1 (COM1), MANUAL_LOG.C2 (COM2), MCU.3 (GND), MCU.5 (AGND), MCU.21 (GND), RTC.5 (NC1), RTC.6 (NC2), RTC.7 (NC3), RTC.8 (NC4), RTC.9 (NC5), RTC.10 (NC6), RTC.11 (NC7), RTC.12 (NC8), RTC.13 (GND), R_REF_A0.1, R_REF_A1.1, R_REF_A2.1, R_REF_A3.1, R_REF_A6.1, R_REF_A7.1, S2.1, S2.2, SD.3 (VSS1), SD.6 (VSS2), SD.GP (GND), SD.GP3 (COMMON_SW), U1.7 (GND1), U1.11 (CTS), U1.18 (GND2), U1.21 (GND3), U1.25 (AGND), U1.26 (TEST), USBD0.2, USBD1.C (-)
INT0: MANUAL_LOG.2 (M2), MCU.32 (PD2(INT0)), RTC.3 (!INT/SQW)
LED+: LED.A, R_LED.2
unnamed: RX.C, U1.22 (RXLED)
unnamed: JP5.D+, U1.15 (USBDP)
unnamed: JP5.D-, U1.16 (USBDM)
unnamed: TX.C, U1.23 (TXLED)
unnamed: RX.A, R_RXLED.2
unnamed: R_TXLED.2, TX.A
unnamed: IC1.4 (STAT), Q2.1 (G), RSTAT.1
unnamed: IC1.5 (GATE), Q1.1 (G)
RESET: C_RESET.2, ISP.5 (RST), MCU.29 (PC6(/RESET)), R_RESET.1, S2.3, S2.4
RX-I: MCU.30 (PD0(RXD)), U1.1 (TXD)
SCL: MCU.28 (PC5(ADC5/SCL)), PU1.1, RTC.16 (SCL)
SDA: MCU.27 (PC4(ADC4/SDA)), PU2.1, RTC.15 (SDA)
SD_CLK: LSHIFT.2 (O), SD.5 (SCLK)
SD_CS: LSHIFT.6 (O), SD.1 (CS)
SD_DI: LSHIFT.4 (O), SD.2 (DATA_IN)
TX-O: MCU.31 (PD1(TXD)), U1.5 (RXD)
VCC: COUT.1, DECOUP.1, H1.3, H1.8, IC1.6 (SEN), ISP.2 (VCC), J1.PWR, LD0_SD.1 (VIN), LD0_SENSE.1 (VIN), L_LPF.1, MCU.4 (VCC), MCU.6 (VCC), PU1.2, PU2.2, Q1.2 (S), Q2.2 (S), RSTAT.2, RTC.2 (VCC), R_RESET.2
VDD: C_LDO_SD.2, LD0_SD.5 (VOUT), LSHIFT.1 (VDD), SD.4 (VDD)
VUSB: JP5.VBUS, Q2.3 (D), R_RXLED.1, R_TXLED.1, U1.4 (VCCIO), U1.20 (VCC), USBD0.1, USBD1.A (+)
X0: CX0.2, MCU.7 (PB6(XTAL1/TOSC1)), XTAL.2
X1: CX1.2, MCU.8 (PB7(XTAL2/TOSC2)), XTAL.1

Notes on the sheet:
VDD = SD3V3
3V3 = Sensor 3V3
Make sure that just this single 1uF cap can handle 2 LDO regulators
